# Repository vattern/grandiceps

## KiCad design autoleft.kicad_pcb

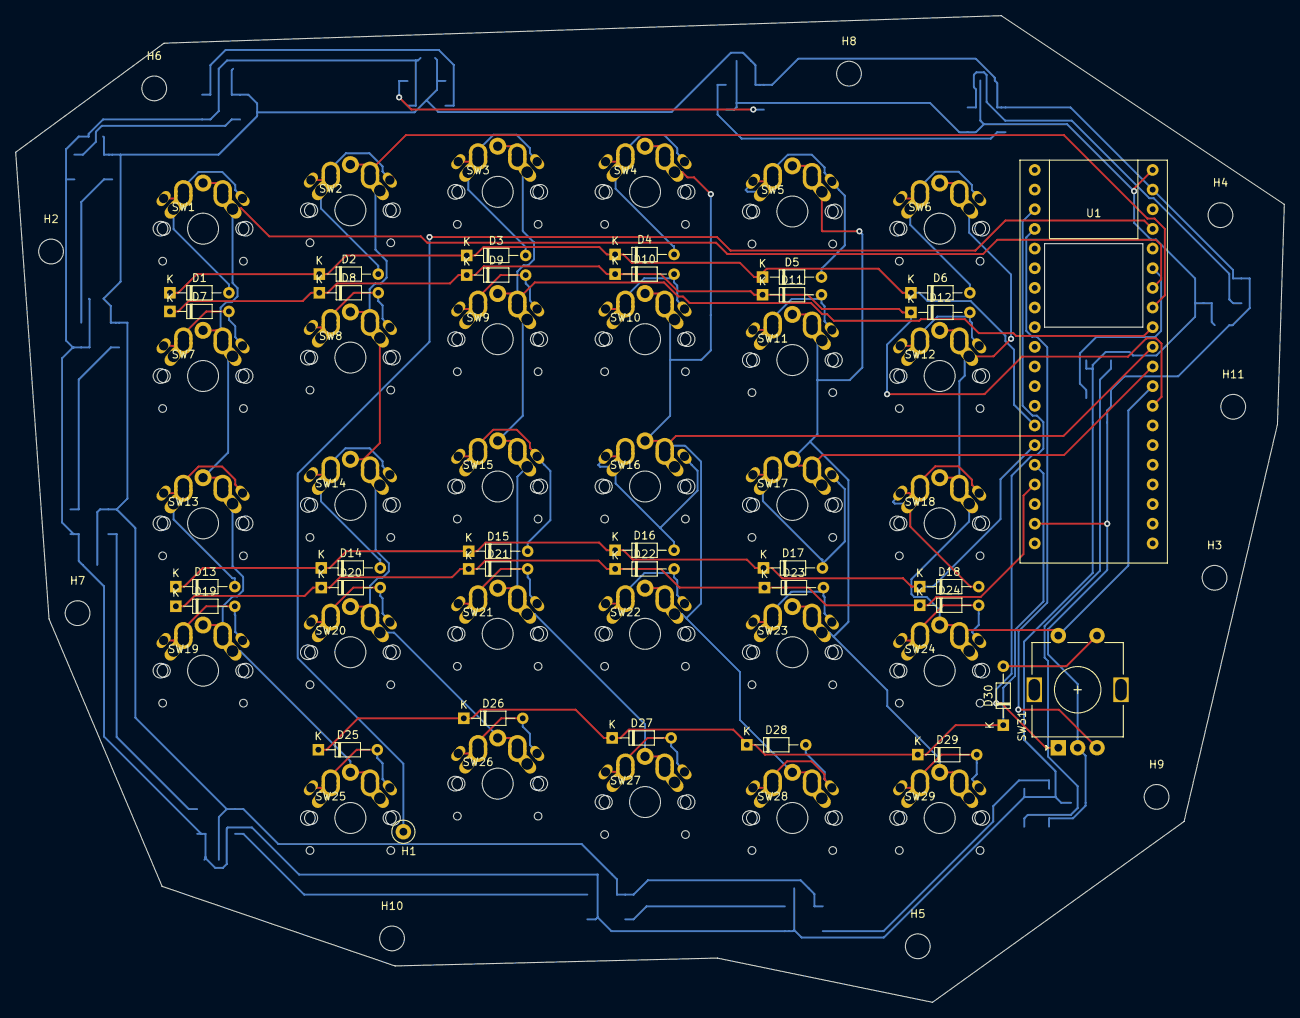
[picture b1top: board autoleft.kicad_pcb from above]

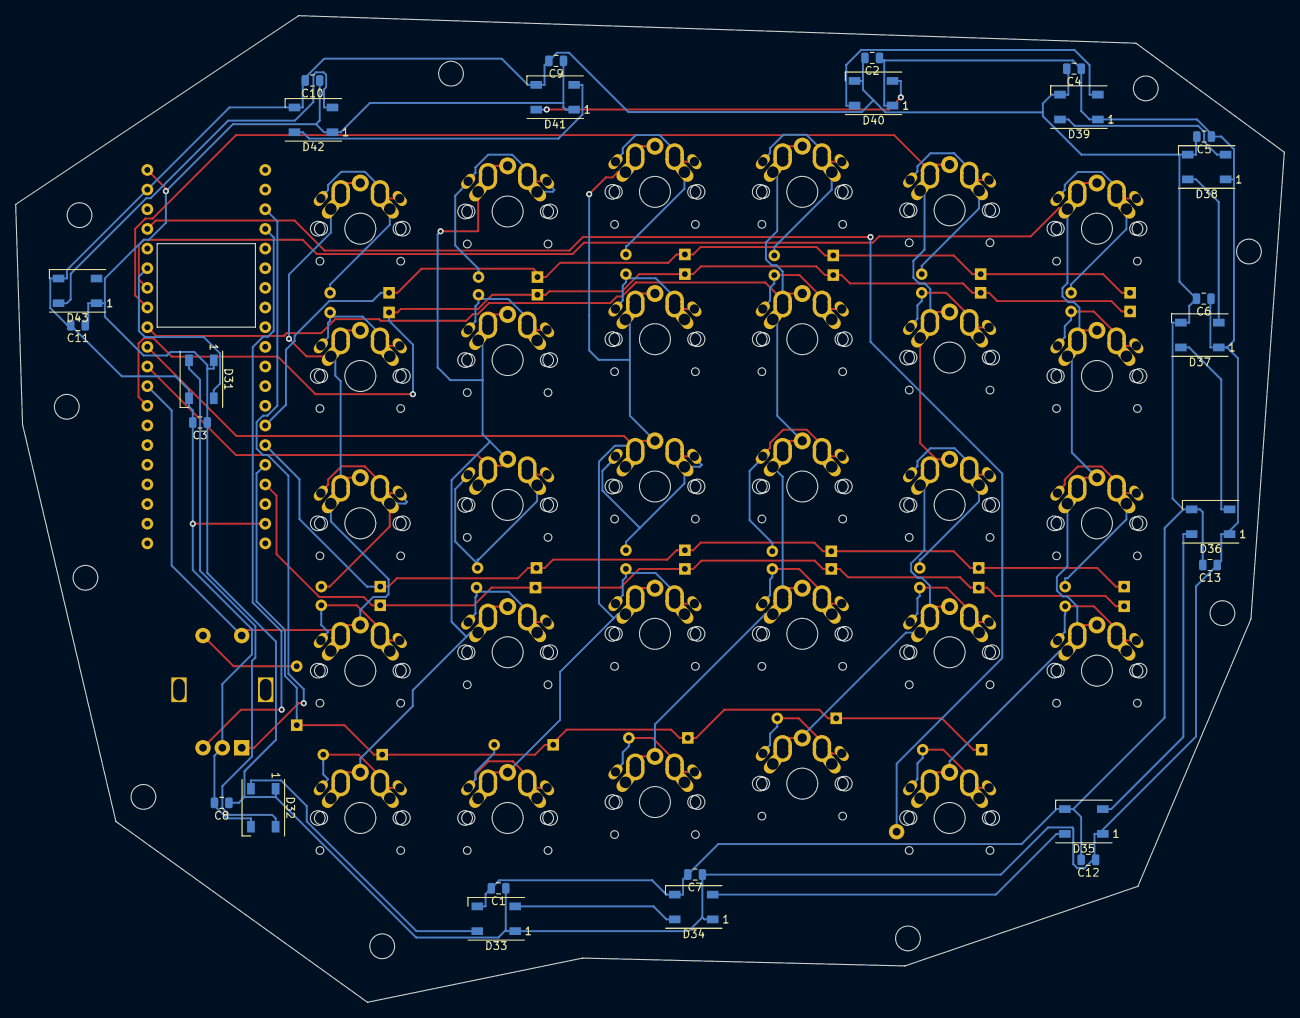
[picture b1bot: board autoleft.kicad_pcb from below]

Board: 2 copper layers, 164.0 x 127.5 mm, 98 parts (26 on the bottom side), 59 nets.

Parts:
C1, C2, C3, C4, C5, C6, C7, C8, C9, C10, C11, C12, C13: 100nF; C_0805_2012Metric
D1, D2, D3, D4, D5, D6, D7, D8, D9, D10, D11, D12, D13, D14, D15, D16, D17, D18, D19, D20, D21, D22, D23, D24, D25, D26, D27, D28, D29, D30: D_Small; D_DO-34_SOD68_P7.62mm_Horizontal
D31, D32, D33, D34, D35, D36, D37, D38, D39, D40, D41, D42, D43: WS2812B; LED_WS2812B_PLCC4_5.0x5.0mm_P3.2mm
H1: MountingHole_Pad; TestPoint_Loop_D2.50mm_Drill1.0mm
H2, H3, H4, H5, H6, H7, H8, H9, H10, H11: MountingHole; MountingHole_3.2mm_M3
SW1: ESC; MX_ALPS_PG1350_noLed
SW2: 1; MX_ALPS_PG1350_noLed
SW3: 2; MX_ALPS_PG1350_noLed
SW4: 3; MX_ALPS_PG1350_noLed
SW5: 4; MX_ALPS_PG1350_noLed
SW6: 5; MX_ALPS_PG1350_noLed
SW7: TAB; MX_ALPS_PG1350_noLed
SW8: Q; MX_ALPS_PG1350_noLed
SW9: W; MX_ALPS_PG1350_noLed
SW10: E; MX_ALPS_PG1350_noLed
SW11: R; MX_ALPS_PG1350_noLed
SW12: T; MX_ALPS_PG1350_noLed
SW13: CAPS; MX_ALPS_PG1350_noLed
SW14: A; MX_ALPS_PG1350_noLed
SW15: S; MX_ALPS_PG1350_noLed
SW16: D; MX_ALPS_PG1350_noLed
SW17: F; MX_ALPS_PG1350_noLed
SW18: G; MX_ALPS_PG1350_noLed
SW19: SHIFT; MX_ALPS_PG1350_noLed
SW20: <; MX_ALPS_PG1350_noLed
SW21: Z; MX_ALPS_PG1350_noLed
SW22, SW28: X; MX_ALPS_PG1350_noLed
SW23, SW29: C; MX_ALPS_PG1350_noLed
SW24: V; MX_ALPS_PG1350_noLed
SW25: CTRL; MX_ALPS_PG1350_noLed
SW26: SUPER; MX_ALPS_PG1350_noLed
SW27: ALT; MX_ALPS_PG1350_noLed
SW31: Rotary_Encoder_Switch; RotaryEncoder_Alps_EC11E-Switch_Vertical_H20mm
U1: WeActBlackPill; Blackpill

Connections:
+5V: C1.1, C2.1, C3.1, C4.1, C5.1, C6.1, C7.1, C8.1, C9.1, C10.1, C11.1, C12.1, C13.1, D31.1, D32.1, D33.1, D34.1, D35.1, D36.1, D37.1, D38.1, D39.1, D40.1, D41.1, D42.1, D43.1, U1.1
GND: C1.2, C2.2, C3.2, C4.2, C5.2, C6.2, C7.2, C8.2, C9.2, C10.2, C11.2, C12.2, C13.2, D31.3, D32.3, D33.3, D34.3, D35.3, D36.3, D37.3, D38.3, D39.3, D40.3, D41.3, D42.3, D43.3, SW31.C, U1.2, U1.22
unnamed: D1.2, SW1.1
unnamed: D2.2, SW2.1
unnamed: D3.2, SW3.1
unnamed: D4.2, SW4.1
unnamed: D5.2, SW5.1
unnamed: D6.2, SW6.1
unnamed: D7.2, SW7.1
unnamed: D8.2, SW8.1
unnamed: D9.2, SW9.1
unnamed: D10.2, SW10.1
unnamed: D11.2, SW11.1
unnamed: D12.2, SW12.1
unnamed: D13.2, SW13.1
unnamed: D14.2, SW14.1
unnamed: D15.2, SW15.1
unnamed: D16.2, SW16.1
unnamed: D17.2, SW17.1
unnamed: D18.2, SW18.1
unnamed: D19.2, SW19.1
unnamed: D20.2, SW20.1
unnamed: D21.2, SW21.1
unnamed: D22.2, SW22.1
unnamed: D23.2, SW23.1
unnamed: D24.2, SW24.1
unnamed: D25.2, SW25.1
unnamed: D26.2, SW26.1
unnamed: D27.2, SW27.1
unnamed: D28.2, SW28.1
unnamed: D29.2, SW29.1
unnamed: D30.2, SW31.S1
unnamed: D31.2, D32.4
unnamed: D32.2, D33.4
unnamed: D33.2, D34.4
unnamed: D34.2, D35.4
unnamed: D35.2, D36.4
unnamed: D36.2, D37.4
unnamed: D37.2, D38.4
unnamed: D38.2, D39.4
unnamed: D39.2, D40.4
unnamed: D40.2, D41.4
unnamed: D41.2, D42.4
unnamed: D42.2, D43.4
unnamed: H1.1, U1.4
RGB: D31.4, U1.6
ROT1A: SW31.A, U1.38
ROT1B: SW31.B, U1.37
col0: SW1.2, SW7.2, SW13.2, SW19.2, SW25.2, U1.7
col1: SW2.2, SW8.2, SW14.2, SW20.2, SW26.2, U1.8
col2: SW3.2, SW9.2, SW15.2, SW21.2, SW27.2, U1.9
col3: SW4.2, SW10.2, SW16.2, SW22.2, SW28.2, U1.10
col4: SW5.2, SW11.2, SW17.2, SW23.2, SW29.2, U1.11
col5: SW6.2, SW12.2, SW18.2, SW24.2, SW31.S2, U1.12
row0: D1.1, D2.1, D3.1, D4.1, D5.1, D6.1, U1.27
row1: D7.1, D8.1, D9.1, D10.1, D11.1, D12.1, U1.13
row2: D13.1, D14.1, D15.1, D16.1, D17.1, D18.1, U1.26
row3: D19.1, D20.1, D21.1, D22.1, D23.1, D24.1, U1.24
row4: D25.1, D26.1, D27.1, D28.1, D29.1, D30.1, U1.25
